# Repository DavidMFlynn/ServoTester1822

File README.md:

# ServoTester1822
Simple R/C Servo tester based on the PIC12F1822

A PCB is comming soon...

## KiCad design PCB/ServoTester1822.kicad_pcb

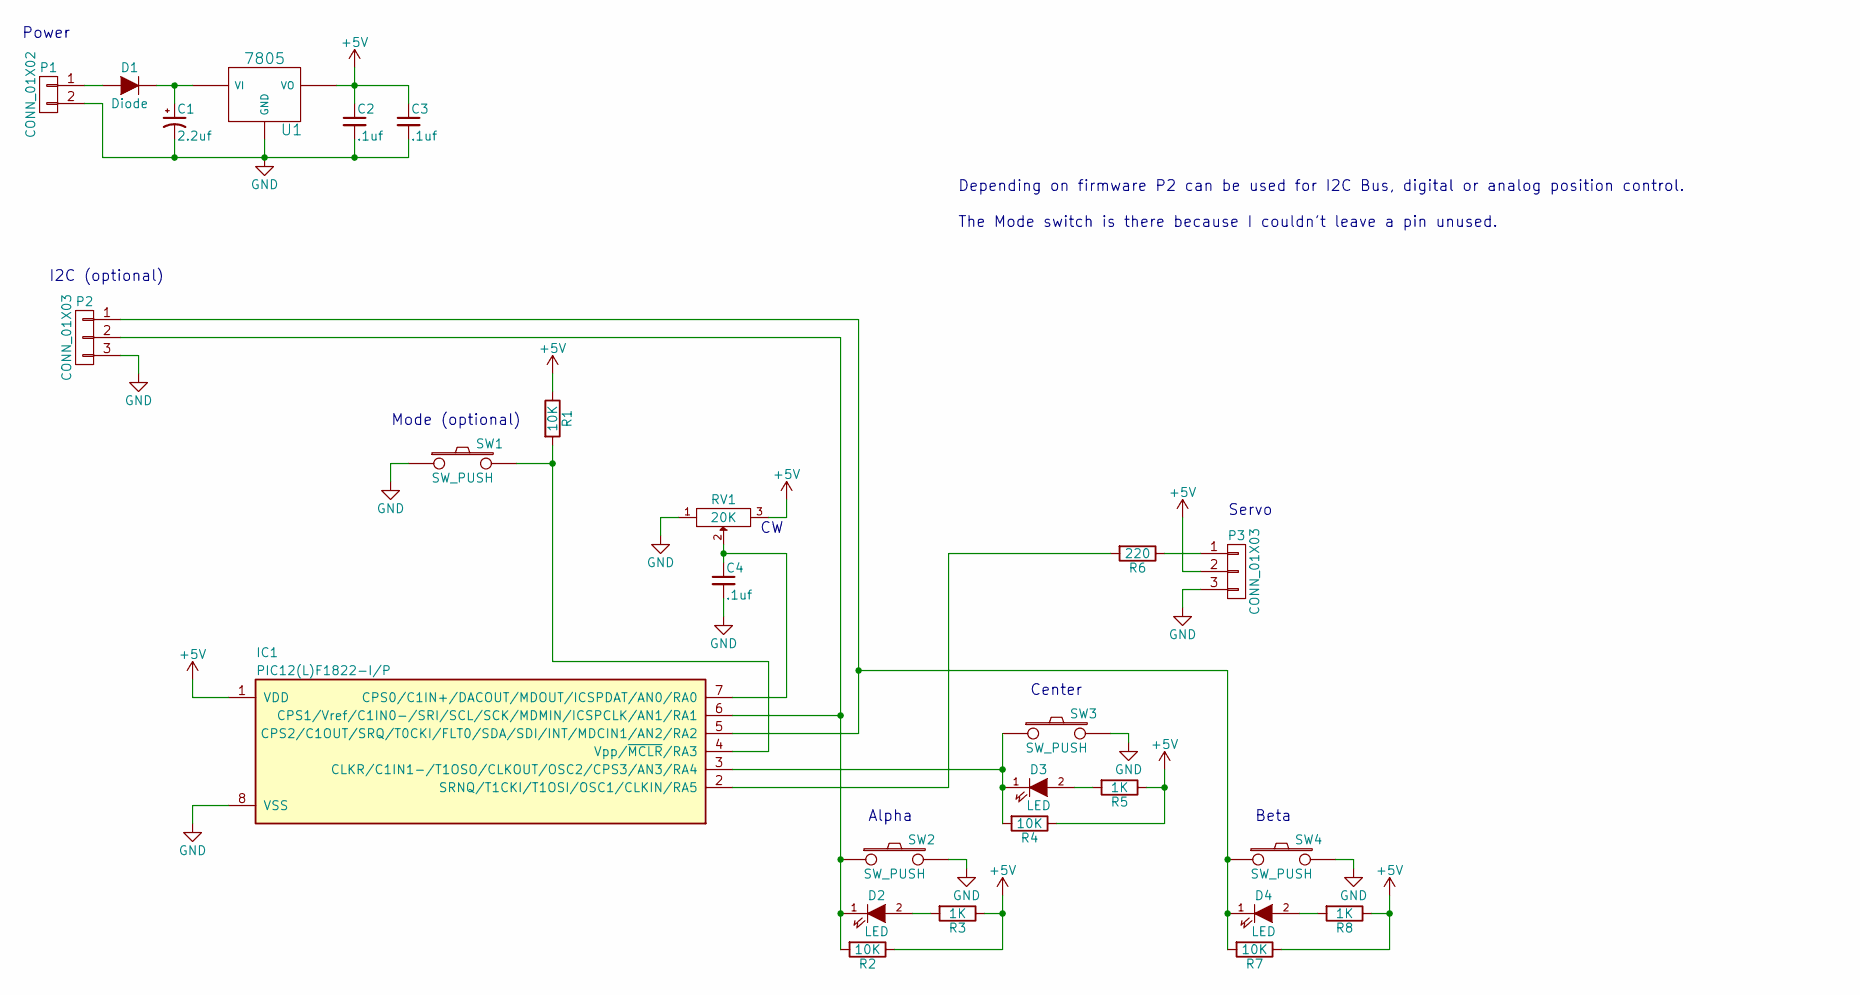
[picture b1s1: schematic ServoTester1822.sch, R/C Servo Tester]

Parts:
C1: 2.2uf; Elko_vert_11x5mm_RM2.5
C2, C3, C4: .1uf; C_0805_HandSoldering
D1: Diode; Diode-SMA_Handsoldering
D2, D3, D4: LED; LED-1206
IC1: PIC12(L)F1822-I/P; DIP-8_W7.62mm
P1: CONN_01X02; bornier2
P2: CONN_01X03; bornier3
P3: CONN_01X03; Pin_Header_Straight_1x03
R1, R2, R4, R7: 10K; R_0805_HandSoldering
R3, R5, R8: 1K; R_0805_HandSoldering
R6: 220; R_0805_HandSoldering
RV1: 20K
SW1, SW2, SW3, SW4: SW_PUSH; SW_SPST_PTS645
U1: 7805; TO-220_Neutral123_Vertical

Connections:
+5V: C2.1, C3.1, IC1.1 (VDD), P3.2, R1.1, R2.1, R3.1, R4.1, R5.1, R7.1, R8.1, RV1.3, U1.VO
GND: C1.2, C2.2, C3.2, C4.2, IC1.8 (VSS), P1.2, P2.3, P3.3, RV1.1, SW1.1, SW2.2, SW3.2, SW4.2, U1.GND
unnamed: C1.1, D1.1 (K), U1.VI
unnamed: C4.1, IC1.7 (CPS0/C1IN+/DACOUT/MDOUT/ICSPDAT/AN0/RA0), RV1.2
unnamed: D1.2 (A), P1.1
unnamed: D2.1 (K), IC1.6 (CPS1/Vref/C1IN0-/SRI/SCL/SCK/MDMIN/ICSP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), P2.2, R2.2, SW2.1
unnamed: D2.2 (A), R3.2
unnamed: D3.1 (K), IC1.3 (CLKR/C1IN1-/T1OSO/CLKOUT/OSC2/CPS3/AN3/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), R4.2, SW3.1
unnamed: D3.2 (A), R5.2
unnamed: D4.1 (K), IC1.5 (CPS2/C1OUT/SRQ/T0CKI/FLT0/SDA/SDI/INT/M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), P2.1, R7.2, SW4.1
unnamed: D4.2 (A), R8.2
unnamed: IC1.2 (SRNQ/T1CKI/T1OSI/OSC1/CLKIN/RA5), R6.2
unnamed: IC1.4 (Vpp/~MCLR~/RA3), R1.2, SW1.2
unnamed: P3.1, R6.1

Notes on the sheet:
Center
Beta
Alpha
I2C (optional)
Power
Servo
Mode (optional)
Depending on firmware P2 can be used for I2C Bus, digital or analog position control.
The Mode switch is there because I couldn't leave a pin unused.

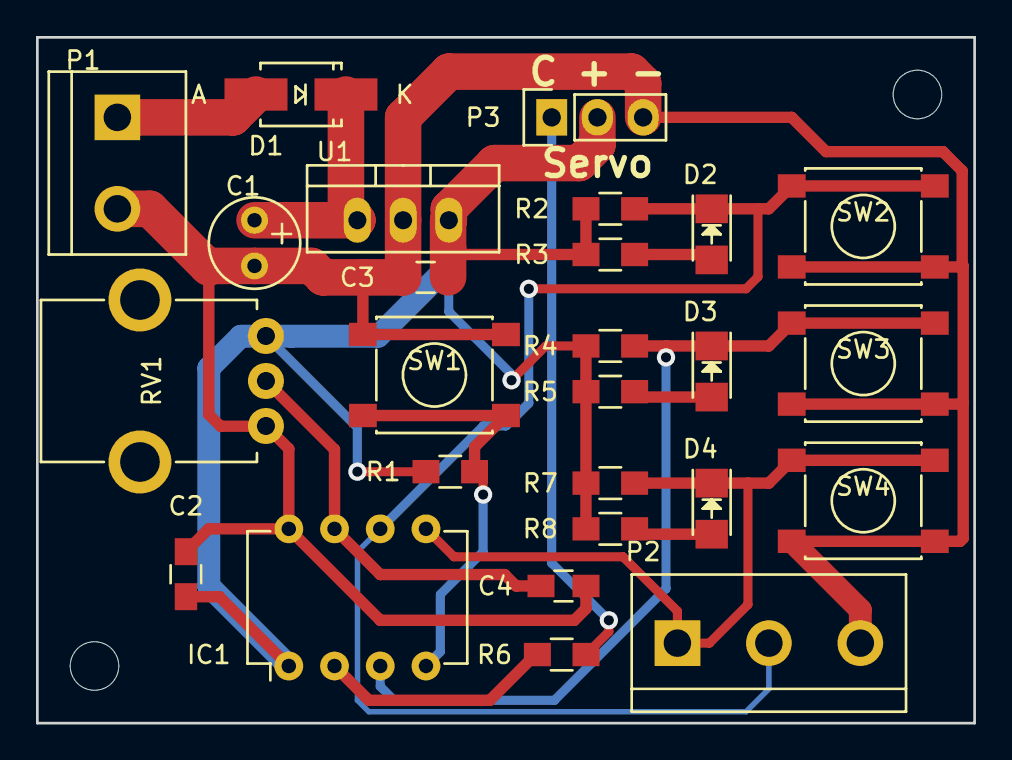
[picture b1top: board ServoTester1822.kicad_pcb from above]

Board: 2 copper layers, 52.1 x 38.1 mm, 28 parts (0 on the bottom side), 14 nets.

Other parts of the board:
H1, H2: MountingHole_2-7mm

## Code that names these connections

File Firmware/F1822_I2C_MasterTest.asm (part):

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;====================================================================================================
;
;  Pin 1 VDD (+5V)		+5V
;  Pin 2 RA5		n/c
;  Pin 3 RA4		System LED Active Low/Center switch Active Low
;  Pin 4 RA3/MCLR*/Vpp (Input only)	n/c
;  Pin 5 RA2		SDA
;  Pin 6 RA1/ICSPCLK		SCL
;  Pin 7 RA0/ICSPDAT		n/c
;  Pin 8 VSS (Ground)		Ground
;
;====================================================================================================
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
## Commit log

2015-09-19 PIC12F1822 R/C Servo tester
    Simple little servo tester.
2015-09-19 Started the PCB
    Schematic is done.
2015-09-19 Started PCB
2015-11-11 Ordered PCB
2015-11-17 Tested with PCB
    No I2C yet, but works for testing and centering servos.
2015-11-17 Simple test version
    lots more to do

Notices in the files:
PCB/ServoTester1822.kicad_pcb:
GPL v2
